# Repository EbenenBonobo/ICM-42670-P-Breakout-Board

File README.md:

# ICM-42670-P-Breakout-Board

Breakout Board Design for the ICM-42670-P but should work with similar ICM 42... Sensors. 
Designed by me, improved by [Reddit](https://www.reddit.com/r/AskElectronics/comments/169lxpz/need_confirmation_for_icm42670p_breakout_board/)

Not tested yet.

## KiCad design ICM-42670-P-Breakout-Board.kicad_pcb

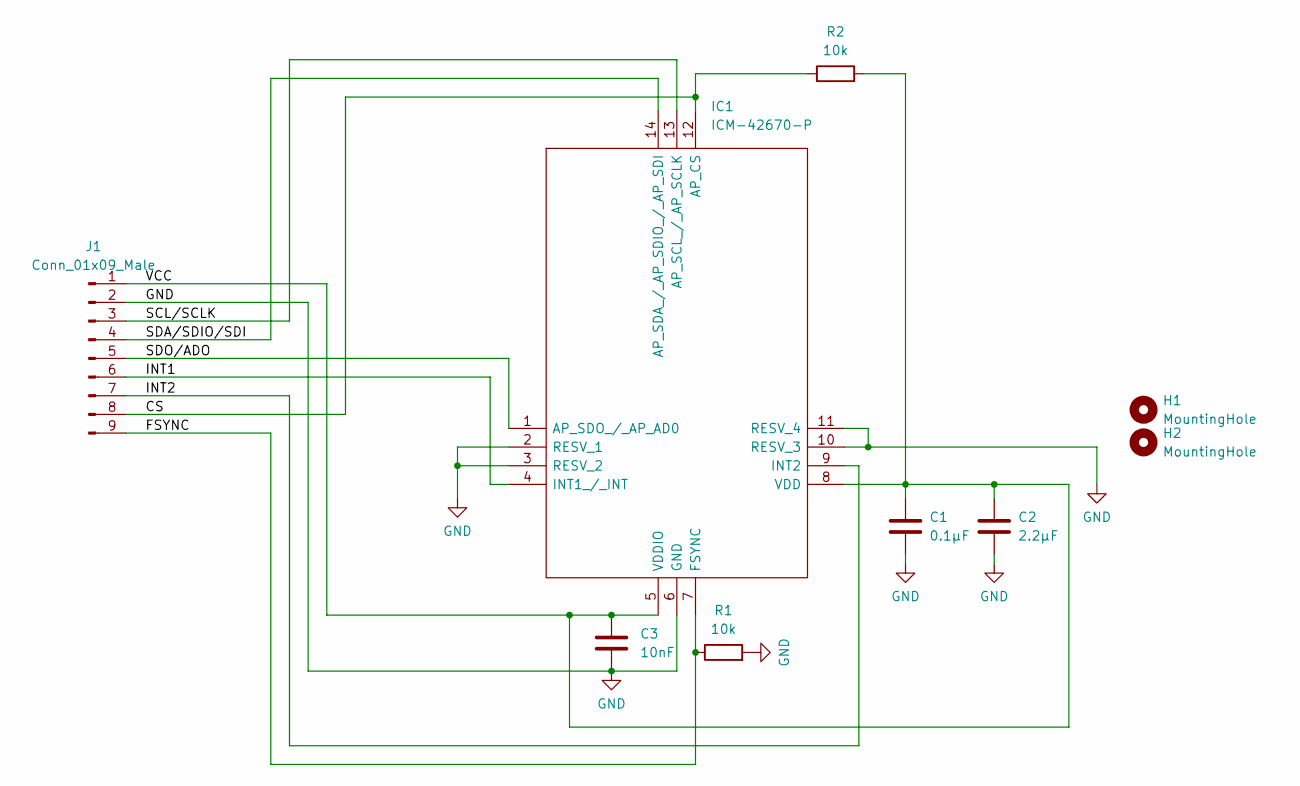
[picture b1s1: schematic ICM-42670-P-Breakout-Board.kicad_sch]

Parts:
C1: 0.1µF; C_0805_2012Metric_Pad1.18x1.45mm_HandSolder
C2: 2.2µF; C_0805_2012Metric_Pad1.18x1.45mm_HandSolder
C3: 10nF; C_0805_2012Metric_Pad1.18x1.45mm_HandSolder
H1, H2: MountingHole; MountingHole_2.2mm_M2_DIN965_Pad_TopBottom
IC1: ICM-42670-P; ICM42670P; Manufacturer_Part_Number ICM-42670-P; Mouser Part Number 410-ICM-42670-P
J1: Conn_01x09_Male; PinHeader_1x09_P2.54mm_Vertical
R1, R2: 10k; R_0805_2012Metric_Pad1.20x1.40mm_HandSolder

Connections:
/CS: IC1.12 (AP_CS), J1.8, R2.1
/FSYNC: IC1.7 (FSYNC), J1.9, R1.1
/INT1: IC1.4 (INT1_/_INT), J1.6
/INT2: IC1.9 (INT2), J1.7
/SCL/SCLK: IC1.13 (AP_SCL_/_AP_SCLK), J1.3
/SDA/SDIO/SDI: IC1.14 (AP_SDA_/_AP_SDIO_/_AP_SDI), J1.4
/SDO/ADO: IC1.1 (AP_SDO_/_AP_AD0), J1.5
/VCC: C1.1, C2.1, C3.1, IC1.5 (VDDIO), IC1.8 (VDD), J1.1, R2.2
GND: C1.2, C2.2, C3.2, IC1.2 (RESV_1), IC1.3 (RESV_2), IC1.6 (GND), IC1.10 (RESV_3), IC1.11 (RESV_4), J1.2, R1.2

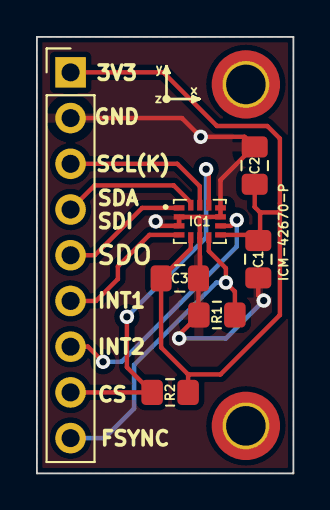
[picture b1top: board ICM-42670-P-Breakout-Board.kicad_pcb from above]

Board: 2 copper layers, 14.2 x 24.2 mm, 9 parts (0 on the bottom side), 9 nets.

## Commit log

2024-09-23 add files for manufacturing
